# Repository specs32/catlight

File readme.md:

# CATLight (Creativity Art Technology)

The new and shiny Flat Flashlight, now featuring:

- ESP32-S2
- MAX77751
- SK6812 + Cree J-Series
- IMU LSM6DS3
- 3000 mAh LiPo (11.5 Wh)
- more to come

Thank you and have a nice day !

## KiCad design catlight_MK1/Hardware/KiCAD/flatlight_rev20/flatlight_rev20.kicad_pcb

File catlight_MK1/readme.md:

# CATLight (Creativity Art Technology)

This is MARK 1 of the new and shiny ESP32-S2 driven flat flashlight (aka flatlight)

The last flatlight revision was 19 ... I changed naming, and revision number from here on.

So this would be the flatlight REV 20

## This Revision contains multiple errors and has many features missing !!

### The first Pancake never gets right ;)

I release it anyways. Its just my dirty Sandbox to get some mud on my fingers !

thank you and have a nice day !

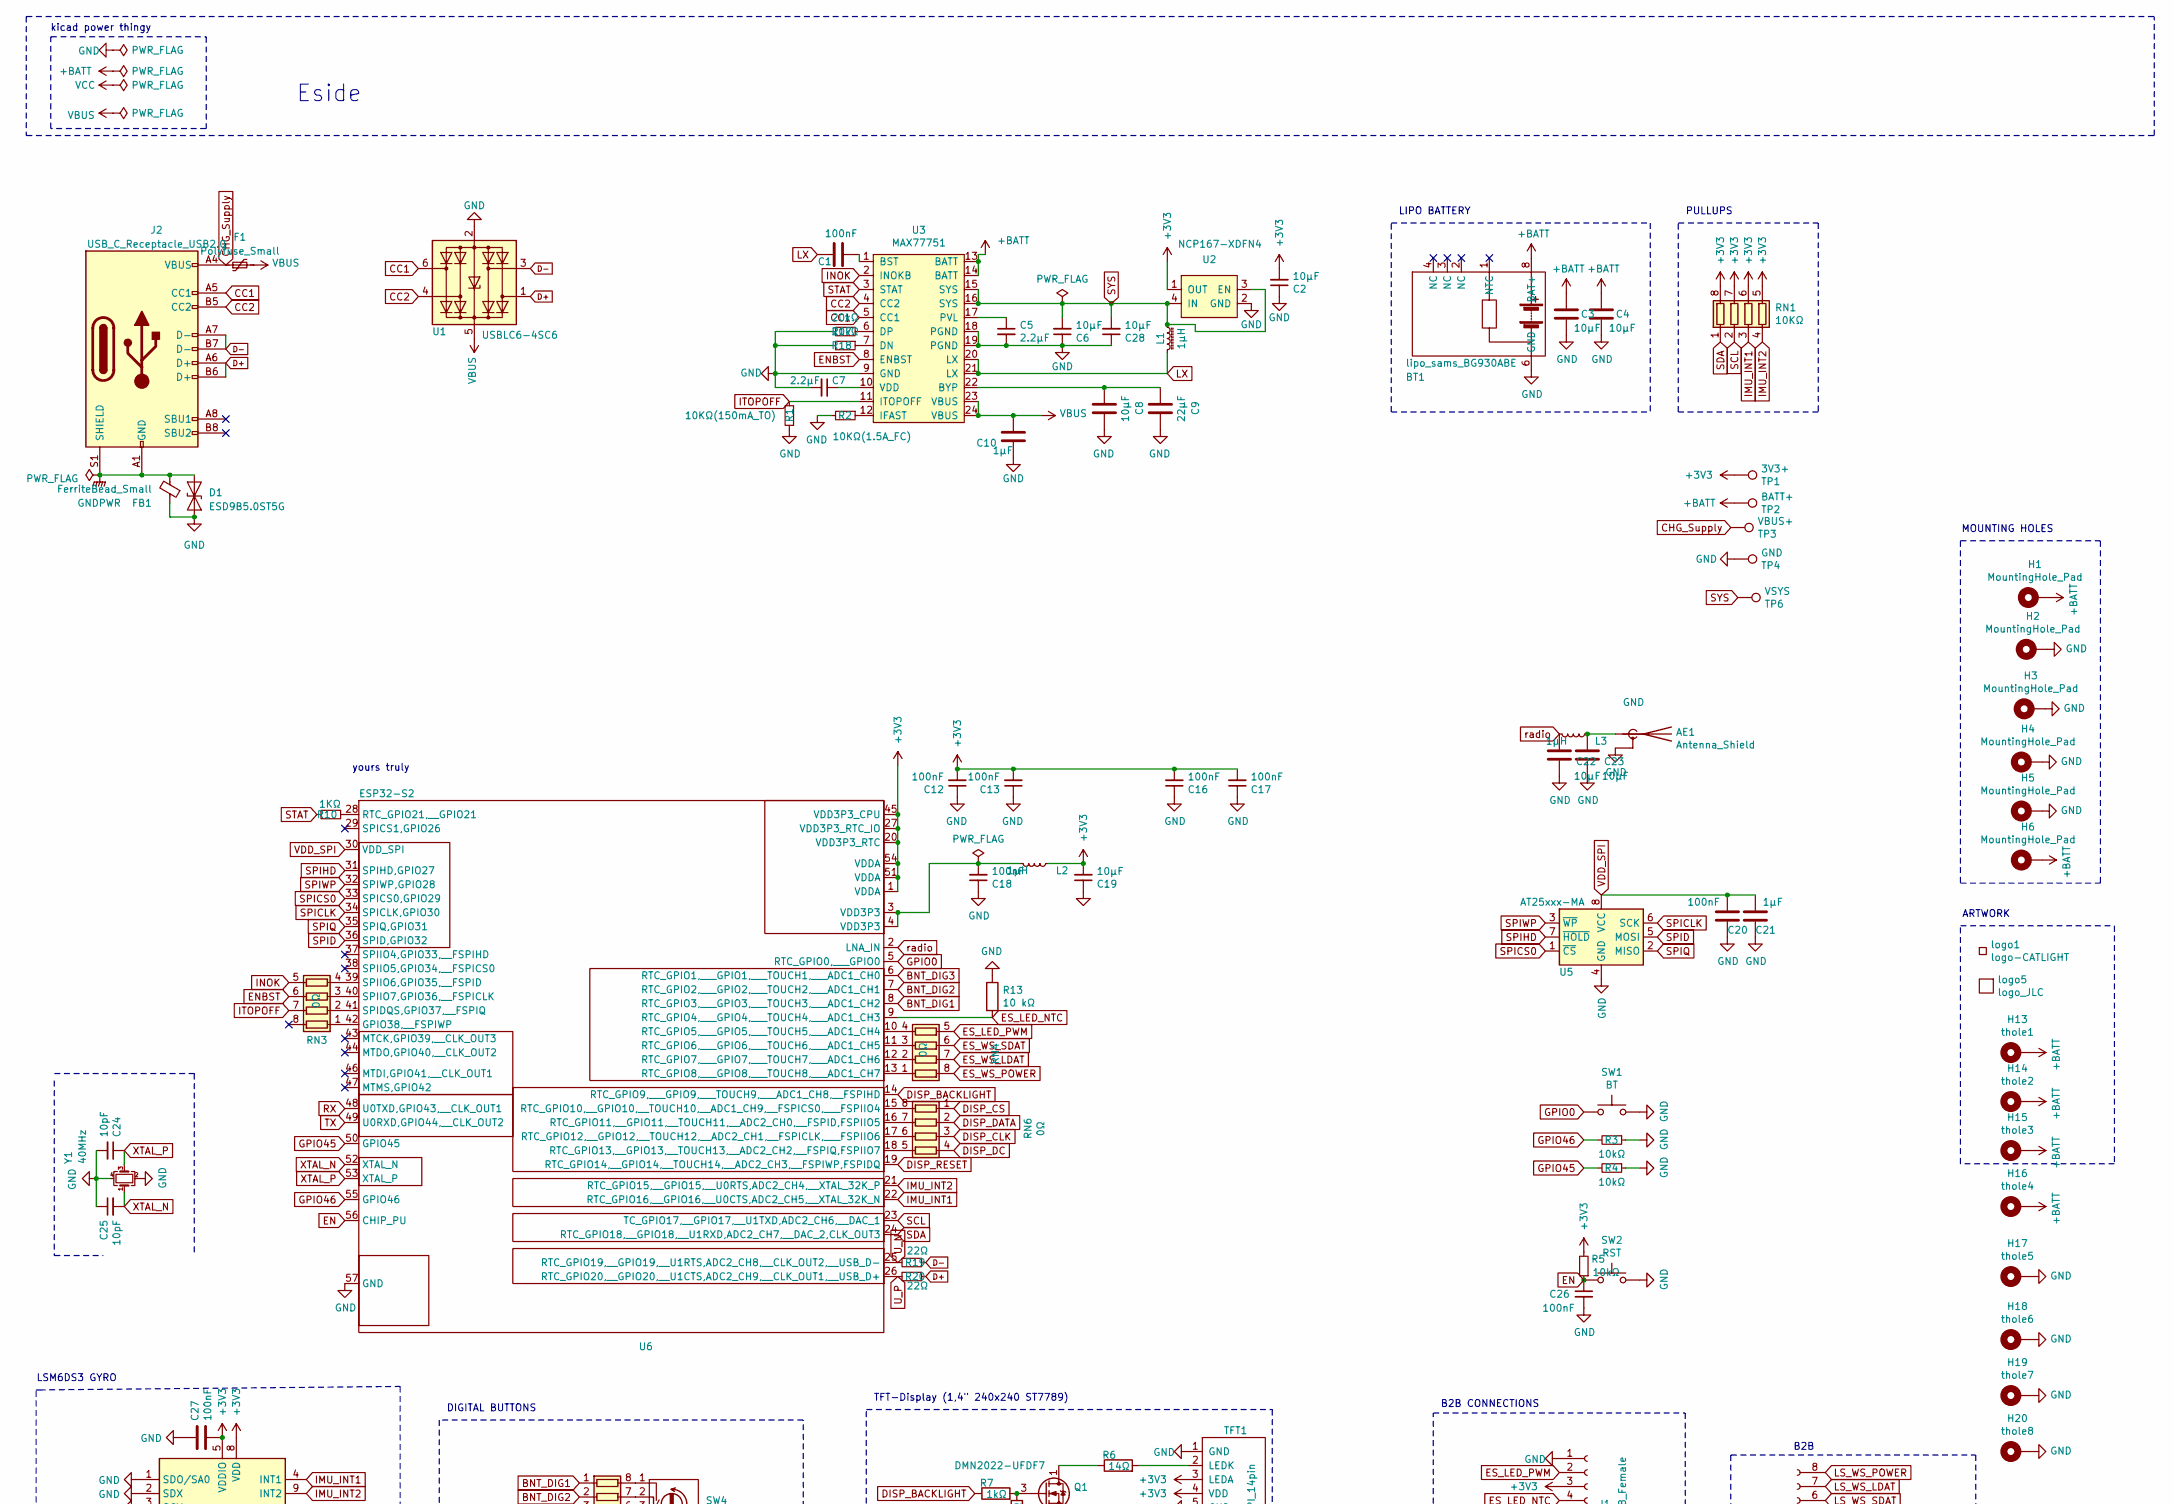
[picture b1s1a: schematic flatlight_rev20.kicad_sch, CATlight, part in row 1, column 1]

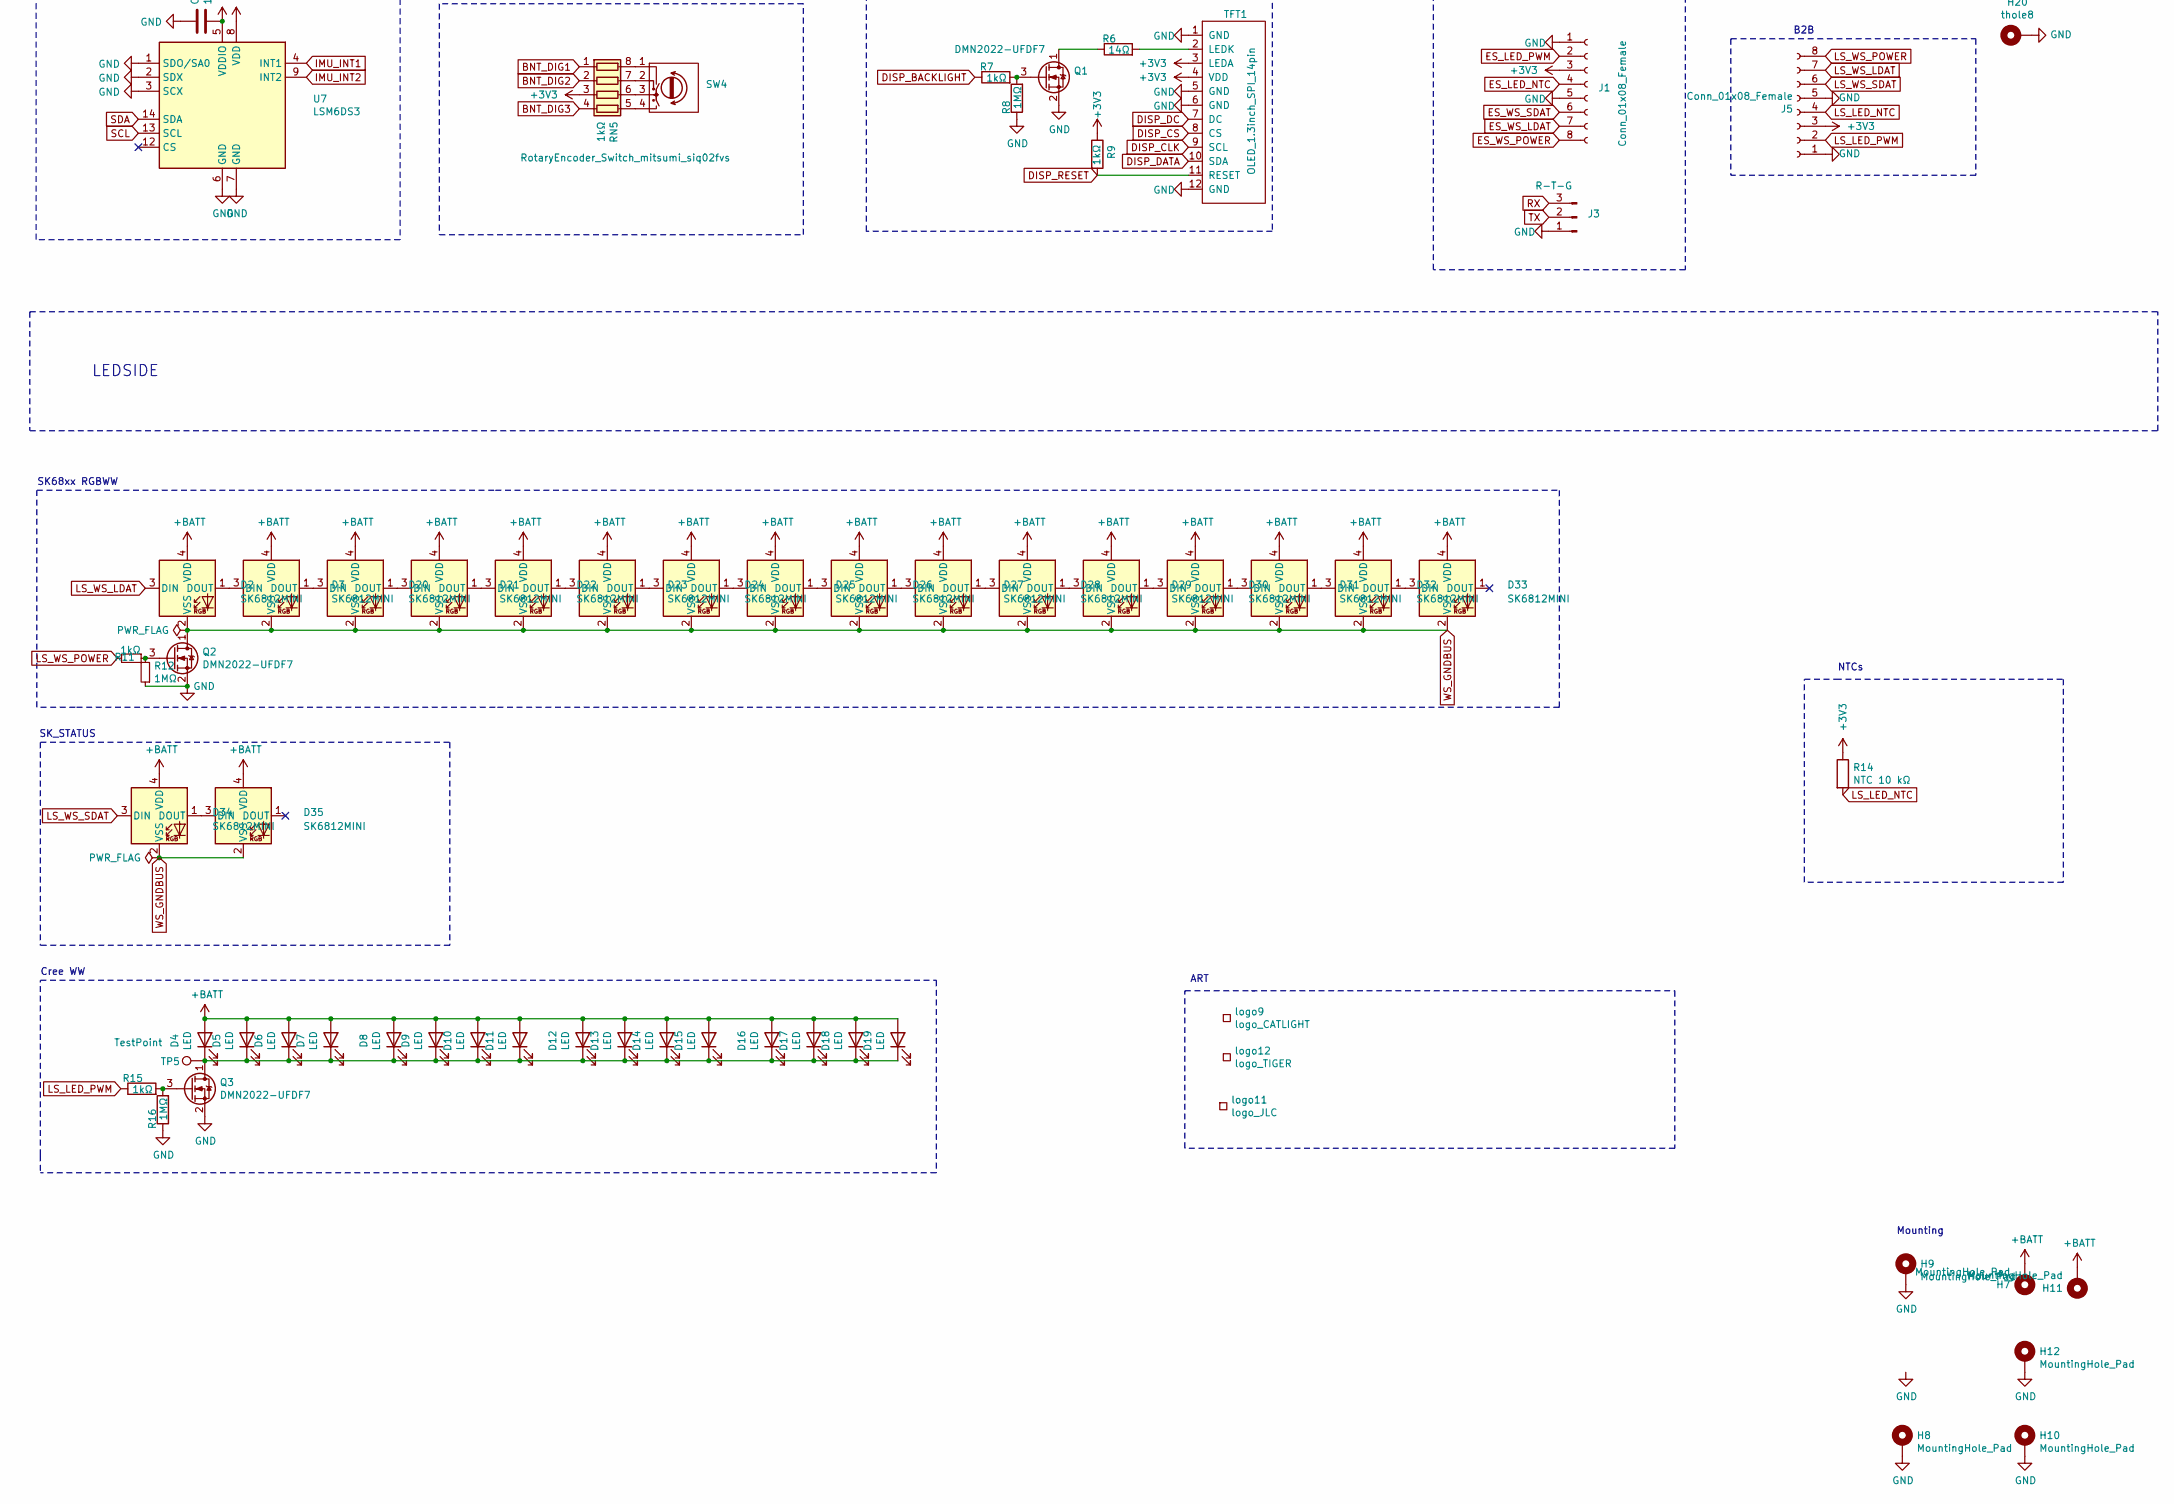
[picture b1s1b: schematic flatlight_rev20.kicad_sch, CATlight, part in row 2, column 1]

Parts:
AE1: Antenna_Shield; Texas_SWRA117D_2.4GHz_Left
BT1: lipo_sams_BG930ABE; lipo_samsung_BG930ABE_double
C1: 100nF; C_0603_1608Metric
C2, C3, C4, C6, C8, C28: 10µF; C_0805_2012Metric
C5, C7: 2.2µF; C_0805_2012Metric
C9: 22µF; C_1210_3225Metric
C10: 1µF; C_0805_2012Metric
C12, C13, C16, C17, C18, C20, C26, C27: 100nF; C_0402_1005Metric
C19, C22, C23: 10µF; C_0603_1608Metric
C21: 1µF; C_0603_1608Metric
C24, C25: 10pF; C_0603_1608Metric
D1: ESD9B5.0ST5G; D_0402_1005Metric_Pad0.77x0.64mm_HandSolder
D2, D20, D21, D22, D23, D24, D25, D26, D27, D28, D29, D30, D31, D32, D33, D34, D35: SK6812MINI; LED_SK6812MINI
D3: SK6812MINI; LED_SK6812MINI_PLCC4_3.5x3.5mm_P1.75mm
D4, D5, D6, D7, D8, D9, D10, D11, D12, D13, D14, D15, D16, D17, D18, D19: LED; LED_Cree-J-Series
F1: Polyfuse_Small; R_0805_2012Metric_Pad1.20x1.40mm_HandSolder
FB1: FerriteBead_Small; R_0805_2012Metric_Pad1.20x1.40mm_HandSolder
H1, H2, H3, H4, H5, H6, H7, H8, H9, H10, H11, H12: MountingHole_Pad; MountingHole_2.2mm_M2_Pad_Via
H13: thole1; plated_hole_1mm
H14: thole2; plated_hole_1mm
H15: thole3; plated_hole_1mm
H16: thole4; plated_hole_1mm
H17: thole5; plated_hole_1mm
H18: thole6; plated_hole_1mm
H19: thole7; plated_hole_1mm
H20: thole8; plated_hole_1mm
J1, J5: Conn_01x08_Female; PinHeader_1x08_P2.00mm_Vertical
J2: USB_C_Receptacle_USB2.0; USB_C_Receptacle_JAE_DX07S016JA1R1500
J3: R-T-G; 01x03_smd_1mmx2mm_pad
L1: 1µH; L_Wuerth_MAPI-4030
L2, L3: 1µH; L_0603_1608Metric
Q1, Q2, Q3: DMN2022-UFDF7; U-DFN2020-6 (Type F)
R1: 10KΩ(150mA_TO); R_0603_1608Metric
R2: 10KΩ(1.5A_FC); R_0603_1608Metric
R3, R4, R5: 10kΩ; R_0603_1608Metric
R6: 14Ω; R_0603_1608Metric
R7, R9, R11, R15: 1kΩ; R_0603_1608Metric
R8, R12, R16: 1MΩ; R_0603_1608Metric
R10: 1KΩ; R_0603_1608Metric
R13: 10 kΩ; R_0603_1608Metric
R14: NTC 10 kΩ; R_0603_1608Metric
R17, R18: 20kΩ; R_0603_1608Metric
R19, R20: 22Ω; R_0603_1608Metric
RN1: 10KΩ; R_Array_Concave_4x0402
RN3, RN4, RN6: 0Ω; R_Array_Concave_4x0402
RN5: 1kΩ; R_Array_Concave_4x0402
SW1: BT; SW_SPST_B3U-1000P
SW2: RST; SW_SPST_B3U-1000P
SW4: RotaryEncoder_Switch_mitsumi_siq02fvs; ROTARY_ENCODER_SIQ_02FVS
TFT1: OLED_1.3inch_SPI_14pin; TFT_1.3inch_spi_12pin_240x240RGB_flat
TP1: 3V3+; TestPoint_Pad_1.0x1.0mm
TP2: BATT+; TestPoint_Pad_1.0x1.0mm
TP3: VBUS+; TestPoint_Pad_1.0x1.0mm
TP4: GND; TestPoint_Pad_1.0x1.0mm
TP5: TestPoint; TestPoint_Pad_1.5x1.5mm
TP6: VSYS; TestPoint_Pad_1.0x1.0mm
U1: USBLC6-4SC6; SOT-23-6
U2: NCP167-XDFN4; UDFN-4-1EP_1x1mm_P0.65mm_EP0.48x0.48mm
U3: MAX77751; max77751
U5: AT25xxx-MA; DFN-8-1EP_3x2mm_P0.5mm_EP1.75x1.45mm
U6: ESP32-S2; QFN-56-1EP_7x7mm_P0.4mm_EP5.6x5.6mm_ThermalVias
U7: LSM6DS3; Bosch_LGA-14_3x2.5mm_P0.5mm
Y1: 40MHz; Crystal_SMD_2520-4Pin_2.5x2.0mm
logo1: logo-CATLIGHT; LOGO_CATLIGHT_4
logo5, logo11: logo_JLC; JLC-SERIAL
logo9: logo_CATLIGHT; LOGO_CATLIGHT_4_small
logo12: logo_TIGER; LOGO_Tiger_1

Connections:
+3V3: C2.2, C12.2, C13.2, C16.2, C17.2, C19.2, C27.2, J1.3, J5.3, L2.1, R5.2, R9.1, R14.1, RN1.5 (R4.2), RN1.6 (R3.2), RN1.7 (R2.2), RN1.8 (R1.2), RN5.3 (R3.1), TFT1.3 (LEDA), TFT1.4 (VDD), TP1.1, U2.1 (OUT), U6.1 (VDDA), U6.20 (VDD3P3_RTC), U6.27 (VDD3P3_RTC_IO), U6.45 (VDD3P3_CPU), U6.51 (VDDA), U6.54 (VDDA), U7.5 (VDDIO), U7.8 (VDD)
+BATT: BT1.7 (BAT+), BT1.8 (BAT+), C3.1, C4.1, D2.4 (VDD), D3.4 (VDD), D4.2 (A), D5.2 (A), D6.2 (A), D7.2 (A), D8.2 (A), D9.2 (A), D10.2 (A), D11.2 (A), D12.2 (A), D13.2 (A), D14.2 (A), D15.2 (A), D16.2 (A), D17.2 (A), D18.2 (A), D19.2 (A), D20.4 (VDD), D21.4 (VDD), D22.4 (VDD), D23.4 (VDD), D24.4 (VDD), D25.4 (VDD), D26.4 (VDD), D27.4 (VDD), D28.4 (VDD), D29.4 (VDD), D30.4 (VDD), D31.4 (VDD), D32.4 (VDD), D33.4 (VDD), D34.4 (VDD), D35.4 (VDD), H1.1, H6.1, H7.1, H11.1, H13.1, H14.1, H15.1, H16.1, TP2.1, U3.13 (BATT), U3.14 (BATT)
BNT_DIG1: RN5.1 (R1.1), U6.8 (RTC_GPIO3,___GPIO3,___TOUCH3,___ADC1_CH2)
BNT_DIG2: RN5.2 (R2.1), U6.7 (RTC_GPIO2,___GPIO2,___TOUCH2,___ADC1_CH1)
BNT_DIG3: RN5.4 (R4.1), U6.6 (RTC_GPIO1,___GPIO1,___TOUCH1,___ADC1_CH0)
CC1: J2.A5 (CC1), U1.6 (I/O4), U3.5 (CC1)
CC2: J2.B5 (CC2), U1.4 (I/O3), U3.4 (CC2)
CHG_Supply: F1.1, J2.A4 (VBUS), J2.A9 (VBUS), J2.B4 (VBUS), J2.B9 (VBUS), TP3.1
D+: J2.A6 (D+), J2.B6 (D+), R20.1, U1.1 (I/O1)
D-: J2.A7 (D-), J2.B7 (D-), R19.1, U1.3 (I/O2)
DISP_BACKLIGHT: R7.1, U6.14 (RTC_GPIO9,___GPIO9,___TOUCH9,___ADC1_CH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)
DISP_CLK: RN6.3 (R3.1), TFT1.9 (SCL)
DISP_CS: RN6.1 (R1.1), TFT1.8 (CS)
DISP_DATA: RN6.2 (R2.1), TFT1.10 (SDA)
DISP_DC: RN6.4 (R4.1), TFT1.7 (DC)
DISP_RESET: R9.2, TFT1.11 (RESET), U6.19 (RTC_GPIO14,__GPIO14,__TOUCH14,__ADC2_CH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)
EN: C26.1, R5.1, SW2.1, U6.56 (CHIP_PU)
ENBST: RN3.6 (R3.2), U3.8 (ENBST)
ES_LED_NTC: J1.4, R13.2, U6.9 (RTC_GPIO4,___GPIO4,___TOUCH4,___ADC1_CH3)
ES_LED_PWM: J1.2, RN4.5 (R4.2)
ES_WS_LDAT: J1.7, RN4.7 (R2.2)
ES_WS_POWER: J1.8, RN4.8 (R1.2)
ES_WS_SDAT: J1.6, RN4.6 (R3.2)
GND: AE1.2 (Shield), BT1.5 (GND), BT1.6 (GND), C2.1, C3.2, C4.2, C5.2, C6.1, C7.2, C8.2, C9.2, C10.1, C12.1, C13.1, C16.1, C17.1, C18.1, C19.1, C20.1, C21.1, C22.1, C23.1, C24.2, C25.1, C26.2, C27.1, C28.1, D1.1 (A1), FB1.1, H2.1, H3.1, H4.1, H5.1, H8.1, H9.1, H10.1, H12.1, H17.1, H18.1, H19.1, H20.1, J1.1, J1.5, J3.1, J5.1, J5.5, Q1.2 (S), Q2.2 (S), Q3.2 (S), R1.1, R2.2, R3.1, R4.1, R8.1, R12.1, R13.1, R16.1, R17.2, R18.2, SW1.2, SW2.2, TFT1.1 (GND), TFT1.5 (GND), TFT1.6 (GND), TFT1.12 (GND), TP4.1, U1.2 (GND), U2.2 (GND), U2.5 (GND), U3.9 (GND), U3.18 (PGND), U3.19 (PGND), U5.4 (GND), U5.9 (GND), U6.57 (GND), U7.1 (SDO/SA0), U7.2 (SDX), U7.3 (SCX), U7.6 (GND), U7.7 (GND), Y1.2, Y1.4
GNDPWR: D1.2 (A2), FB1.2, J2.A1 (GND), J2.A12 (GND), J2.B1 (GND), J2.B12 (GND), J2.S1 (SHIELD)
GPIO0: SW1.1, U6.5 (RTC_GPIO0,___GPIO0)
GPIO45: R4.2, U6.50 (GPIO45)
GPIO46: R3.2, U6.55 (GPIO46)
IMU_INT1: RN1.3 (R3.1), U6.22 (RTC_GPIO16,__GPIO16,__U0CTS,ADC2_CH5,__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), U7.4 (INT1)
IMU_INT2: RN1.4 (R4.1), U6.21 (RTC_GPIO15,__GPIO15,__U0RTS,ADC2_CH4,__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), U7.9 (INT2)
INOK: RN3.5 (R4.2), U3.2 (INOKB)
ITOPOFF: R1.2, RN3.7 (R2.2), U3.11 (ITOPOFF)
LS_LED_NTC: J5.4, R14.2
LS_LED_PWM: J5.2, R15.1
LS_WS_LDAT: D2.3 (DIN), J5.7
LS_WS_POWER: J5.8, R11.2
LS_WS_SDAT: D34.3 (DIN), J5.6
LX: C1.2, L1.2, U3.20 (LX), U3.21 (LX)
unnamed: AE1.1 (A), C23.2, L3.1
unnamed: C1.1, U3.1 (BST)
unnamed: C5.1, U3.17 (PVL)
unnamed: C7.1, U3.10 (VDD)
unnamed: C8.1, C9.1, U3.22 (BYP)
unnamed: C18.2, L2.2, U6.3 (VDD3P3), U6.4 (VDD3P3)
unnamed: D2.1 (DOUT), D3.3 (DIN)
unnamed: D4.1 (K), D5.1 (K), D6.1 (K), D7.1 (K), D8.1 (K), D9.1 (K), D10.1 (K), D11.1 (K), D12.1 (K), D13.1 (K), D14.1 (K), D15.1 (K), D16.1 (K), D17.1 (K), D18.1 (K), D19.1 (K), Q3.1 (D), TP5.1
unnamed: D20.1 (DOUT), D21.3 (DIN)
unnamed: D3.1 (DOUT), D20.3 (DIN)
unnamed: D21.1 (DOUT), D22.3 (DIN)
unnamed: D22.1 (DOUT), D23.3 (DIN)
unnamed: D23.1 (DOUT), D24.3 (DIN)
unnamed: D24.1 (DOUT), D25.3 (DIN)
unnamed: D25.1 (DOUT), D26.3 (DIN)
unnamed: D26.1 (DOUT), D27.3 (DIN)
unnamed: D27.1 (DOUT), D28.3 (DIN)
unnamed: D28.1 (DOUT), D29.3 (DIN)
unnamed: D29.1 (DOUT), D30.3 (DIN)
unnamed: D30.1 (DOUT), D31.3 (DIN)
unnamed: D31.1 (DOUT), D32.3 (DIN)
unnamed: D32.1 (DOUT), D33.3 (DIN)
unnamed: D34.1 (DOUT), D35.3 (DIN)
unnamed: Q1.1 (D), R6.1
unnamed: Q1.3 (G), R7.2, R8.2
unnamed: Q2.3 (G), R11.1, R12.2
unnamed: Q3.3 (G), R15.2, R16.2
unnamed: R2.1, U3.12 (IFAST)
unnamed: R6.2, TFT1.2 (LEDK)
unnamed: R10.1, U6.28 (RTC_GPIO21,__GPIO21)
unnamed: R17.1, U3.6 (DP)
unnamed: R18.1, U3.7 (DN)
unnamed: RN3.1 (R1.1), U6.42 (GPIO38,__FSPIWP)
unnamed: RN3.2 (R2.1), U6.41 (SPIDQS,GPIO37,__FSPIQ)
unnamed: RN3.3 (R3.1), U6.40 (SPIIO7,GPIO36,__FSPICLK)
unnamed: RN3.4 (R4.1), U6.39 (SPIIO6,GPIO35,__FSPID)
unnamed: RN4.1 (R1.1), U6.13 (RTC_GPIO8,___GPIO8,___TOUCH8,___ADC1_CH7)
unnamed: RN4.2 (R2.1), U6.12 (RTC_GPIO7,___GPIO7,___TOUCH7,___ADC1_CH6)
unnamed: RN4.3 (R3.1), U6.11 (RTC_GPIO6,___GPIO6,___TOUCH6,___ADC1_CH5)
unnamed: RN4.4 (R4.1), U6.10 (RTC_GPIO5,___GPIO5,___TOUCH5,___ADC1_CH4)
unnamed: RN5.5 (R4.2), SW4.4 (B)
unnamed: RN5.6 (R3.2), SW4.3 (C)
unnamed: RN5.7 (R2.2), SW4.2 (S)
unnamed: RN5.8 (R1.2), SW4.1 (A)
unnamed: RN6.5 (R4.2), U6.18 (RTC_GPIO13,__GPIO13,__TOUCH13,__ADC2_CH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)
unnamed: RN6.6 (R3.2), U6.17 (RTC_GPIO12,__GPIO12,__TOUCH12,__ADC2_CH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)
unnamed: RN6.7 (R2.2), U6.16 (RTC_GPIO11,__GPIO11,__TOUCH11,__ADC2_CH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)
unnamed: RN6.8 (R1.2), U6.15 (RTC_GPIO10,__GPIO10,__TOUCH10,__ADC1_CH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)
RX: J3.3, U6.48 (U0TXD,GPIO43,__CLK_OUT1)
SCL: RN1.2 (R2.1), U6.23 (TC_GPIO17,__GPIO17,__U1TXD,ADC2_CH6,__D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), U7.13 (SCL)
SDA: RN1.1 (R1.1), U6.24 (RTC_GPIO18,__GPIO18,__U1RXD,ADC2_CH7,__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), U7.14 (SDA)
SPICLK: U5.6 (SCK), U6.34 (SPICLK,GPIO30)
SPICS0: U5.1 (~CS), U6.33 (SPICS0,GPIO29)
SPID: U5.5 (MOSI), U6.36 (SPID,GPIO32)
SPIHD: U5.7 (~HOLD), U6.31 (SPIHD,GPIO27)
SPIQ: U5.2 (MISO), U6.35 (SPIQ,GPIO31)
SPIWP: U5.3 (~WP), U6.32 (SPIWP,GPIO28)
STAT: R10.2, U3.3 (STAT)
SYS: C6.2, C28.2, L1.1, TP6.1, U2.3 (EN), U2.4 (IN), U3.15 (SYS), U3.16 (SYS)
TX: J3.2, U6.49 (U0RXD,GPIO44,__CLK_OUT2)
U_N: R19.2, U6.25 (RTC_GPIO19,__GPIO19,__U1RTS,ADC2_CH8,__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)
U_P: R20.2, U6.26 (RTC_GPIO20,__GPIO20,__U1CTS,ADC2_CH9,__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)
VBUS: C10.2, F1.2, U1.5 (VBUS), U3.23 (VBUS), U3.24 (VBUS)
VDD_SPI: C20.2, C21.2, U5.8 (VCC), U6.30 (VDD_SPI)
WS_GNDBUS: D2.2 (VSS), D3.2 (VSS), D20.2 (VSS), D21.2 (VSS), D22.2 (VSS), D23.2 (VSS), D24.2 (VSS), D25.2 (VSS), D26.2 (VSS), D27.2 (VSS), D28.2 (VSS), D29.2 (VSS), D30.2 (VSS), D31.2 (VSS), D32.2 (VSS), D33.2 (VSS), D34.2 (VSS), D35.2 (VSS), Q2.1 (D)
XTAL_N: C25.2, U6.52 (XTAL_N), Y1.1
XTAL_P: C24.1, U6.53 (XTAL_P), Y1.3
radio: C22.2, L3.2, U6.2 (LNA_IN)

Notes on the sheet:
LSM6DS3 GYRO
SK68xx RGBWW
kicad power thingy
Cree WW
SK_STATUS
LEDSIDE
yours truly
Eside
DIGITAL BUTTONS
TFT-Display (1,4" 240x240 ST7789)
ART
LIPO BATTERY
B2B CONNECTIONS
PULLUPS
B2B
NTCs
Mounting
MOUNTING HOLES
ARTWORK

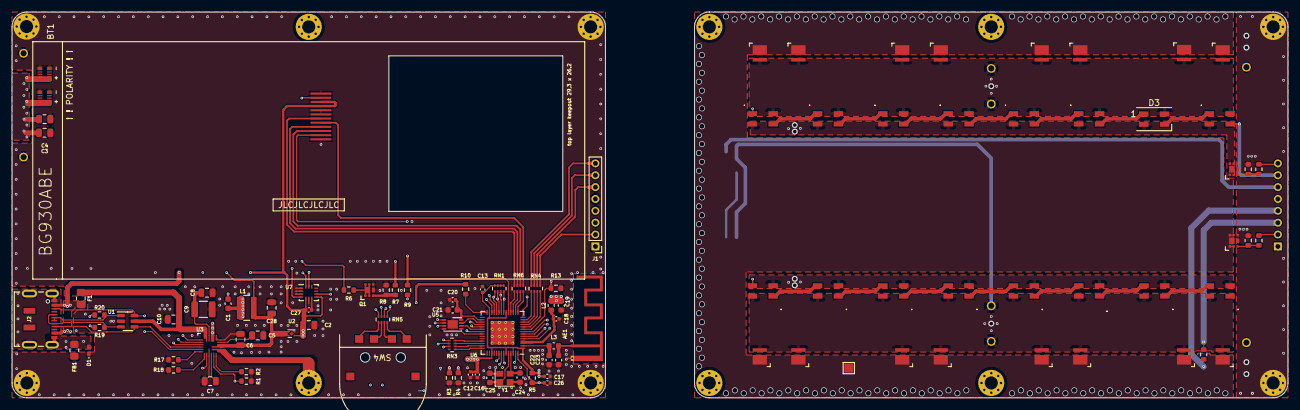
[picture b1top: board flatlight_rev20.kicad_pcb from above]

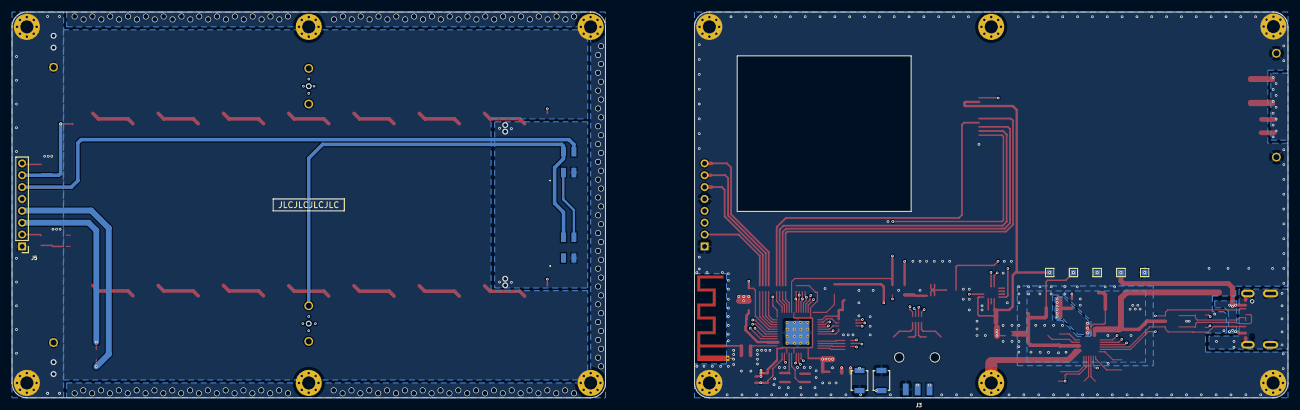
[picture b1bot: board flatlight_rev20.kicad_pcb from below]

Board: 4 copper layers, 215.0 x 65.0 mm, 141 parts (15 on the bottom side), 106 nets.

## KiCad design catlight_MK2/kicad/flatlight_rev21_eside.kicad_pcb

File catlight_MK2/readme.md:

# CATLight (Creativity Art Technology)

This is MARK 2 of the new and shiny ESP32-S2 driven flat flashlight (aka flatlight)

This is a close proximity Flashlight, it has no lense to focus a beam, but it smoothly lights up a wide field around you. I find it perfect for indoor usage (searching dark drawers in the cellar and so on, but it also lights your way to the shed at night..)

Features : 
- USB-C power delivery standard realized with a MAX77751 (fast charge + PD (boost mode 5V up to 1 Amp))
- ESP32-S2 with wifi etc...
- 1.2 " TFT SPI color display
- 1 IMU LSM6DS3 or LSM6DSM .. both will work with slight changes in the initialization
- 1 CREE XLAMP with a DIO5661 flash driver and protective lens (no focus) that delivers up to 1.5 Amps into the XLAMP.. makes for a nice foto flash ..
- 16 neopixels on there 2 rows by 8.. i think it is possible to realize a POV display with it since there also is a LSM6DS3 IMU on there.
- 10 Duris high power LEDs (100mA each) this is the main light source (300 mA J-Series are no longer available.. sadly !)
- 4 TEMP sensors on the light. 2 NTCs close to critical places (XLAMP and Duris LEDS) 1 in the ESP itself and on in the IMU.
- Battery Voltage measuring (resistor divider on analog 1)

### This Revision works ! 

... with no errors as far as I can see and test (I own no OSZI ;))

There is one thing though... the Antenna matching Network works better if you put a cap in series and the coil in the first place to ground. (swap C24 with L3)

This revision works with WLED beta 2 (0.13.0-b2) there are filesystem issues, but the default install seems to work and you can save the LED settings and power off / on again and it maintains theses settings even there is no "official" support for the ESP32-S2 yet.
MAYBE I will fork and branch and modify and write a usermod for wled in the future. Maybe...
For now there is rudimentary arduino firmware in the arduino folder.
There is a platformio_override.ini in the base Folder I used to compile WLED with in code OSS with platformio under arch linux.

#### WARNING !!! WARNING !!! WARNING !!! WARNING !!! WARNING !!! WARNING !!! WARNING !!! WARNING !!! 

DO NOT put too much capacitance on the LED side, it will mess with the soft latch ! 1µF per duris LED is sufficient and works.
If you put a lot of high value CAPs on the LED side you need to lower the value of R5. (1.2KΩ with 25 µF on the LED side. Flash and array)

the duris LEDs are mosfet driven and that is their ONE and ONLY current limiter, a duty cycle of 30 % on a full lipo makes a nice bright light.
if you pull up the mosfet with 100 % duty cycle it make a smoldered PCB with the LEDs falling off and molten solder dripping everywhere... 
probably a good idea to keep that in mind when fumbling with the firmware...
___

there is a footprint for additional flash memory with a solder bridge CS0/CS1 parallel to the internal flash. if you have an ESP32-S2 without flash you can put a flash chip here (AT256Q i think) please refer to the flash compatibility list for the ESP32-S2 on the espressif website.

wifi standby time with a genuine LIPO Battery is 60+ hours

USB-C fast charging works up to 2.5 Ampere !! (almost full in 60 minutes ;))
the MAX 77751 supports pass through and power delivery, so you can charge your phne on the light in an emerrgency !

Please keep in mind that this project is my private experiment and CC-BY-NC-SA !
If you blow up your toaster .. not my fault.

the overall development cost was 600 €, the cost per CATLight (PCB + parts + 3dprint) is around 50 € assembly time is 6-8 hours if you do it 100% by hand.

Have fun emitting Bosons of differend wavelength..

made with <3 btw!

#### Special thanks to Lisa who provided all the cat drawings !!!
___
___

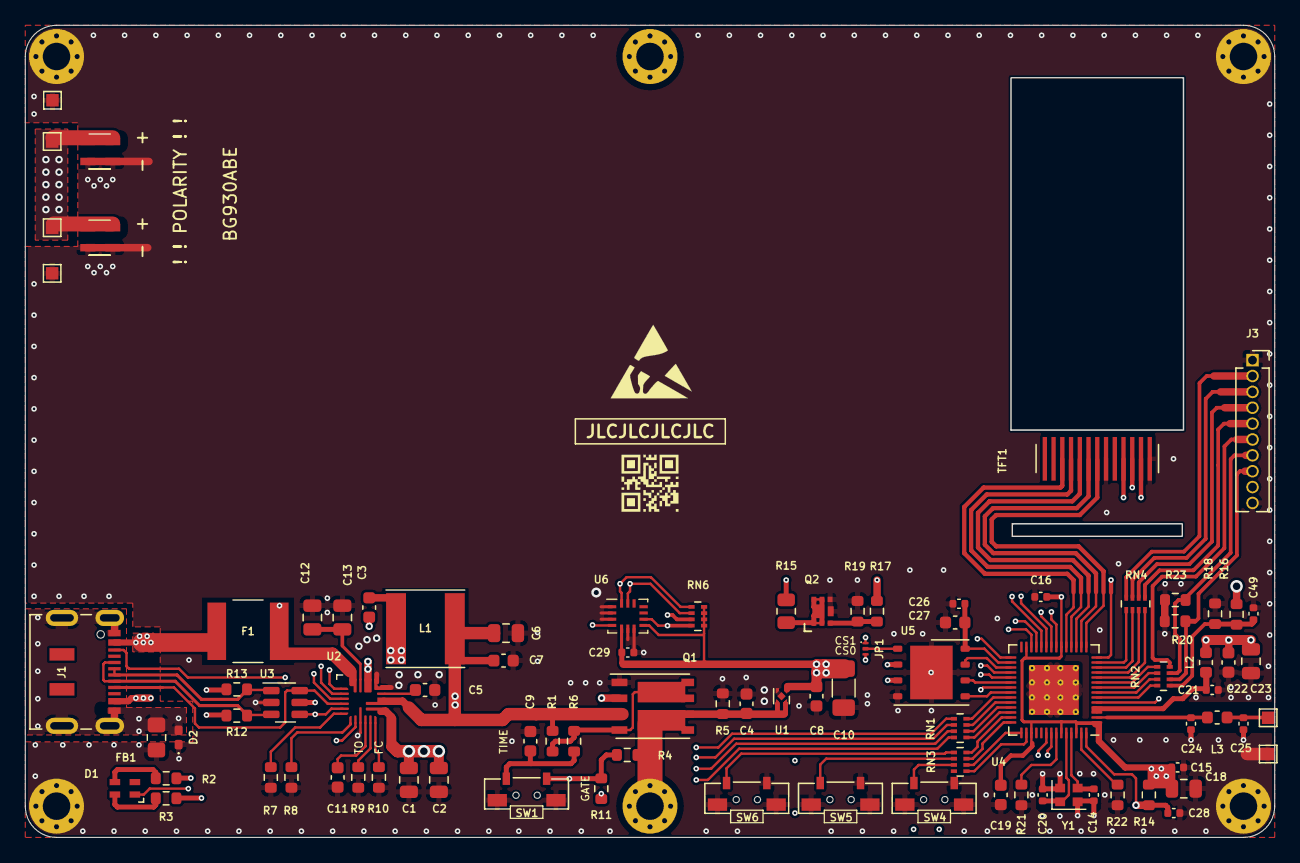
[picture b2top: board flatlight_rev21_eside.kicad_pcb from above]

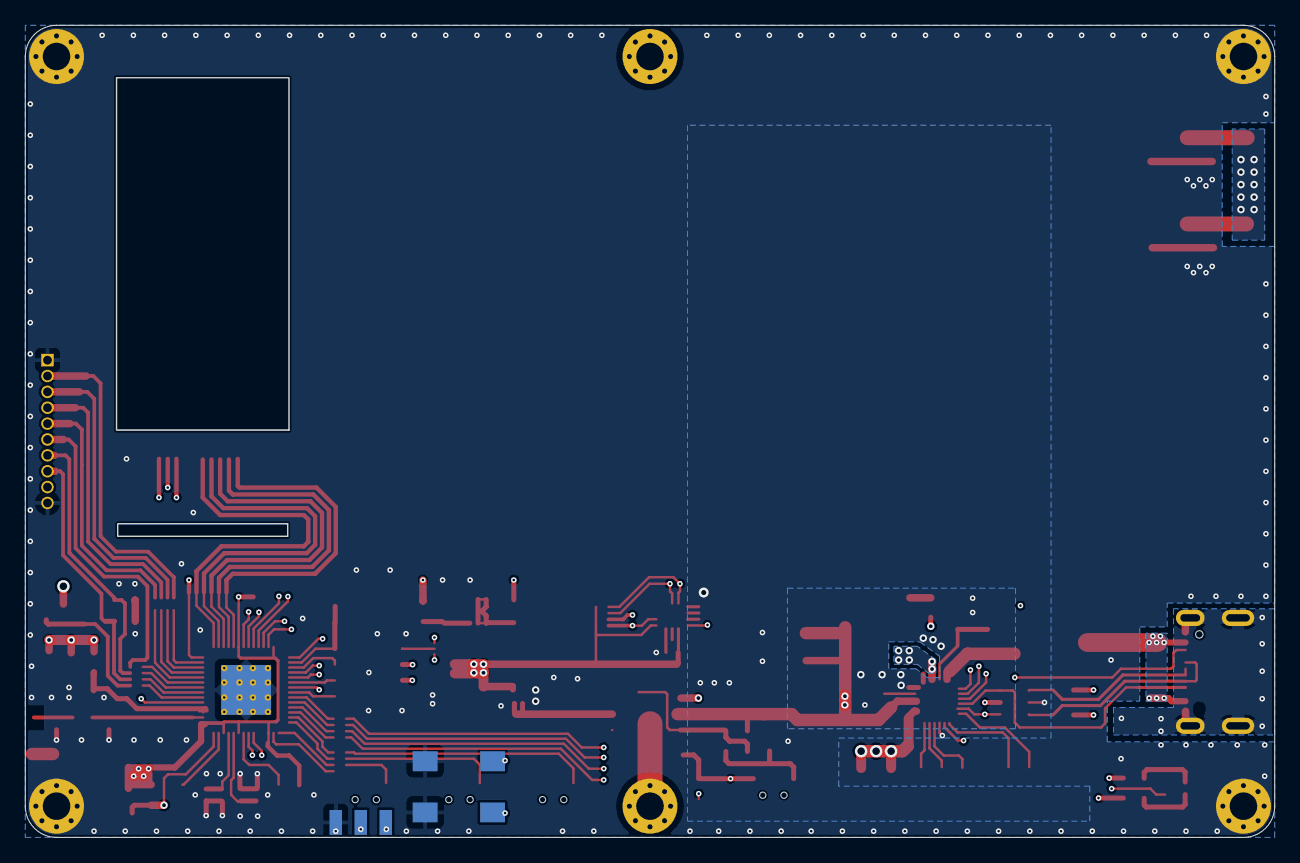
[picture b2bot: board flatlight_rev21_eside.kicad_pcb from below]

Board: 4 copper layers, 100.0 x 65.0 mm, 102 parts (5 on the bottom side), 92 nets.

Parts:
BT1: lipo_sams_BG930ABE; lipo_samsung_BG930ABE_double
C1, C2, C6, C12, C18, C23: 10µF; C_0805_2012Metric
C3: 100nF; C_0603_1608Metric
C4, C7, C8, C9, C19, C22, C27: 1µF; C_0603_1608Metric
C5, C11: 2.2µF; C_0603_1608Metric
C10: 10µF; C_1206_3216Metric_Pad1.33x1.80mm_HandSolder
C13: 22µF; C_0805_2012Metric
C14, C20: 10pF; C_0402_1005Metric
C15, C16, C21, C26, C28, C29, C49: 100nF; C_0402_1005Metric
C24, C25: 4,7 pF; C_0402_1005Metric
D1: LED_ABRG; 0606_ARGB_LED
D2: ESD9B5.0ST5G; D_0402_1005Metric_Pad0.77x0.64mm_HandSolder
F1: Polyfuse_Small; FUSE_littlefuse_2016-4.1x5.2mm
FB1: FerriteBead_Small; R_0805_2012Metric_Pad1.20x1.40mm_HandSolder
H1, H2, H3, H4, H5, H6: MountingHole_Pad; MountingHole_2.2mm_M2_Pad_Via
J1: USB_C_Receptacle_USB2.0; USB_C_Receptacle_JAE_DX07S016JA1R1500
J2: G-T-R; 01x03_smd_1mmx2mm_pad
J3: B2B_eside; PinSocket_1x10_P1.27mm_Vertical
JP1: SolderJumper_3_Open; microbridge
L1: 1µH; L_Taiyo-Yuden_NR-60xx
L2: 1µH; L_0603_1608Metric
L3: 1.8 nH; L_0603_1608Metric
Q1: DMC1016UPD; PowerDI5060-8
Q2: DMN2022-UFDF7; U-DFN2020-6 (Type F)
R1, R4, R14, R21, R22: 10kΩ; R_0603_1608Metric
R2, R3: 1KΩ; R_0603_1608Metric
R5: 10kΩ (depending on caps); R_0603_1608Metric
R6: 100kΩ; R_0603_1608Metric
R7, R8: 20kΩ; R_0603_1608Metric
R9: 10KΩ(150mA_TO); R_0603_1608Metric
R10: 10KΩ(1.5A_FC); R_0603_1608Metric
R11: 0 Ω; R_0603_1608Metric
R12, R13: 22Ω; R_0603_1608Metric
R15: 14Ω; R_0805_2012Metric
R16, R18, R19: 1MΩ; R_0603_1608Metric
R17: 1kΩ; R_0603_1608Metric
R20, R23: 10 kΩ; R_0603_1608Metric
RN1, RN2, RN3: 0Ω; R_Array_Concave_4x0402
RN4: 1kΩ; R_Array_Concave_4x0402
RN6: 10KΩ; R_Array_Concave_4x0402
SW1, SW4, SW5, SW6: BTN_PWR; white_nano_smd_switch
SW2: BT; SW_SPST_EVQPE1
SW3: RST; SW_SPST_EVQPE1
TFT1: OLED_ST7735_0.9inch_SPI_13pin; TFT_ST7735_0,96_160x80_folded
TP6: ANT_H; TestPoint_Pad_1.0x1.0mm
TP8: ANT_GND; TestPoint_Pad_1.0x1.0mm
TP11, TP12: GND; TestPoint_Pad_1.0x1.0mm
TP13, TP14: +BATT; TestPoint_Pad_1.0x1.0mm
U1: NCP167-XDFN4; UDFN-4-1EP_1x1mm_P0.65mm_EP0.48x0.48mm
U2: MAX77751; max77751
U3: USBLC6-4SC6; SOT-23-6
U4: ESP32-S2; QFN-56-1EP_7x7mm_P0.4mm_EP5.6x5.6mm_ThermalVias
U5: AT25xxx-MA; WSON-8-1EP_6x5mm_P1.27mm_EP3.4x4.3mm
U6: LSM6DS3; Bosch_LGA-14_3x2.5mm_P0.5mm
Y1: 40MHz; Crystal_SMD_2016-4Pin_2.0x1.6mm_smallpads
logo1: logo_qrtag; logo_QR_url_git_catlight
logo2: logo_JLC; JLC-SERIAL
logo6: logo_esd; ESD-Logo_6.6x6mm_SilkScreen
logo8: logo_heart; logo_heart3
logo10: logo_CATLIGHT; logo_catlightMK2_small

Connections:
+3V3: C8.2, C10.2, C15.2, C16.2, C18.2, C19.2, C22.2, C23.2, C29.2, J3.9, L2.1, R14.2, RN6.5 (R4.2), RN6.6 (R3.2), RN6.7 (R2.2), RN6.8 (R1.2), TFT1.10 (VCC), TFT1.12 (LEDA), U1.1 (OUT), U4.1 (VDDA), U4.20 (VDD3P3_RTC), U4.27 (VDD3P3_RTC_IO), U4.45 (VDD3P3_CPU), U4.51 (VDDA), U4.54 (VDDA), U6.5 (VDDIO), U6.8 (VDD)
+BATT: BT1.7 (+), BT1.8 (+), C1.2, C2.2, R16.2, TP13.1, TP14.1, U2.13 (BATT), U2.14 (BATT)
ADC_BATV: C49.1, R16.1, R18.2, RN2.5 (R4.2)
BNT_DIG1: RN3.5 (R4.2), SW6.2
BNT_DIG2: RN3.6 (R3.2), SW5.2
BNT_DIG3: RN3.7 (R2.2), SW4.2
CC1: J1.A5 (CC1), U2.5 (CC1), U3.4 (I/O3)
CC2: J1.B5 (CC2), U2.4 (CC2), U3.6 (I/O4)
D+: J1.A6 (D+), J1.B6 (D+), R13.1, U3.1 (I/O1)
D-: J1.A7 (D-), J1.B7 (D-), R12.1, U3.3 (I/O2)
DISP_BACKLIGHT: R17.1, U4.14 (RTC_GPIO9,___GPIO9,___TOUCH9,___ADC1_CH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)
DISP_CLK: TFT1.4 (SCK), U4.18 (RTC_GPIO13,__GPIO13,__TOUCH13,__ADC2_CH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)
DISP_CS: TFT1.7 (CS), U4.15 (RTC_GPIO10,__GPIO10,__TOUCH10,__ADC1_CH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)
DISP_DATA: TFT1.3 (MOSI), U4.19 (RTC_GPIO14,__GPIO14,__TOUCH14,__ADC2_CH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)
DISP_DC: TFT1.5 (RS), U4.17 (RTC_GPIO12,__GPIO12,__TOUCH12,__ADC2_CH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)
DISP_RESET: TFT1.6 (RES), U4.16 (RTC_GPIO11,__GPIO11,__TOUCH11,__ADC2_CH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)
EN: C28.1, R14.1, SW3.1, U4.56 (CHIP_PU)
ENBST: RN1.5 (R4.2), U2.8 (ENBST)
ES_FLASH_EN: J3.3, RN4.7 (R2.2)
ES_JS_LED_NTC: J3.8, R20.2, RN2.6 (R3.2)
ES_LED_PWM: J3.2, RN4.8 (R1.2)
ES_TORCH_EN: J3.4, RN4.6 (R3.2)
ES_WS_LDAT: J3.5, RN4.5 (R4.2)
ES_WS_POWER: J3.6, RN2.8 (R1.2)
ES_XP_LED_NTC: J3.7, R23.2, RN2.7 (R2.2)
GND: BT1.5 (-), BT1.6 (-), C1.1, C2.1, C4.1, C5.2, C6.1, C7.1, C8.1, C9.2, C10.1, C11.2, C12.2, C13.2, C14.2, C15.1, C16.1, C18.1, C19.1, C20.1, C21.1, C22.1, C23.1, C24.1, C25.1, C26.1, C27.1, C28.2, C29.1, C49.2, D2.1 (A1), FB1.1, H2.1, H3.1, H4.1, H5.1, J2.1, J3.1, J3.10, Q1.1 (S), Q2.2 (S), R5.2, R7.2, R8.2, R9.1, R10.2, R18.1, R19.1, R20.1, R21.1, R22.1, R23.1, SW1.3, SW2.2, SW3.2, SW4.1, SW4.3, SW5.1, SW5.3, SW6.1, SW6.3, TFT1.8 (GND), TFT1.13 (GND), TP8.1, TP11.1, TP12.1, U1.2 (GND), U1.5 (GND), U2.9 (GND), U2.18 (PGND), U2.19 (PGND), U3.2 (GND), U4.57 (GND), U5.4 (GND), U5.9 (GND), U6.1 (SDO/SA0), U6.2 (SDX), U6.3 (SCX), U6.6 (GND), U6.7 (GND), Y1.2, Y1.4
GNDPWR: D2.2 (A2), FB1.2, J1.A1 (GND), J1.A12 (GND), J1.B1 (GND), J1.B12 (GND), J1.S1 (SHIELD)
GPIO0: SW2.1, U4.5 (RTC_GPIO0,___GPIO0)
GPIO45: R21.2, U4.50 (GPIO45)
GPIO46: R22.2, U4.55 (GPIO46)
IMU_INT1: RN6.3 (R3.1), U4.22 (RTC_GPIO16,__GPIO16,__U0CTS,ADC2_CH5,__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), U6.4 (INT1)
IMU_INT2: RN6.4 (R4.1), U4.21 (RTC_GPIO15,__GPIO15,__U0RTS,ADC2_CH4,__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), U6.9 (INT2)
INOK: R2.2, RN1.7 (R2.2), U2.2 (INOKB)
LX: C3.2, L1.2, U2.20 (LX), U2.21 (LX)
unnamed: C3.1, U2.1 (BST)
unnamed: C5.1, U2.17 (PVL)
unnamed: C9.1, R6.2, SW1.2
unnamed: C11.1, U2.10 (VDD)
unnamed: C12.1, C13.1, U2.22 (BYP)
unnamed: C21.2, L2.2, U4.3 (VDD3P3), U4.4 (VDD3P3)
unnamed: C25.2, L3.1, TP6.1
unnamed: D1.3 (RK), R3.1
unnamed: D1.4 (GK), R2.1
unnamed: F1.1, J1.A4 (VBUS), J1.A9 (VBUS), J1.B4 (VBUS), J1.B9 (VBUS)
unnamed: JP1.2 (C), U5.1 (~CS)
unnamed: Q1.2 (G), R4.2, R11.1, SW1.1
unnamed: Q1.4 (G), Q1.7 (D), Q1.8 (D), R1.2, R6.1
unnamed: Q2.1 (D), R15.2
unnamed: Q2.3 (G), R17.2, R19.2
unnamed: R7.1, U2.6 (DP)
unnamed: R8.1, U2.7 (DN)
unnamed: R9.2, U2.11 (ITOPOFF)
unnamed: R10.1, U2.12 (IFAST)
unnamed: R15.1, TFT1.11 (LEDK)
unnamed: RN1.1 (R1.1), U4.40 (SPIIO7,GPIO36,__FSPICLK)
unnamed: RN1.2 (R2.1), U4.39 (SPIIO6,GPIO35,__FSPID)
unnamed: RN1.3 (R3.1), U4.38 (SPIIO5,GPIO34,__FSPICS0)
unnamed: RN1.4 (R4.1), U4.37 (SPIIO4,GPIO33,__FSPIHD)
unnamed: RN2.1 (R1.1), U4.9 (RTC_GPIO4,___GPIO4,___TOUCH4,___ADC1_CH3)
unnamed: RN2.2 (R2.1), U4.8 (RTC_GPIO3,___GPIO3,___TOUCH3,___ADC1_CH2)
unnamed: RN2.3 (R3.1), U4.7 (RTC_GPIO2,___GPIO2,___TOUCH2,___ADC1_CH1)
unnamed: RN2.4 (R4.1), U4.6 (RTC_GPIO1,___GPIO1,___TOUCH1,___ADC1_CH0)
unnamed: RN3.1 (R1.1), U4.44 (MTDO,GPIO40,__CLK_OUT2)
unnamed: RN3.2 (R2.1), U4.43 (MTCK,GPIO39,__CLK_OUT3)
unnamed: RN3.3 (R3.1), U4.42 (GPIO38,__FSPIWP)
unnamed: RN3.4 (R4.1), U4.41 (SPIDQS,GPIO37,__FSPIQ)
unnamed: RN4.1 (R1.1), U4.13 (RTC_GPIO8,___GPIO8,___TOUCH8,___ADC1_CH7)
unnamed: RN4.2 (R2.1), U4.12 (RTC_GPIO7,___GPIO7,___TOUCH7,___ADC1_CH6)
unnamed: RN4.3 (R3.1), U4.11 (RTC_GPIO6,___GPIO6,___TOUCH6,___ADC1_CH5)
unnamed: RN4.4 (R4.1), U4.10 (RTC_GPIO5,___GPIO5,___TOUCH5,___ADC1_CH4)
PWRMAIN_SW: R11.2, RN1.8 (R1.2)
RX: J2.3, U4.48 (U0TXD,GPIO43,__CLK_OUT1)
SCL: RN6.2 (R2.1), U4.23 (TC_GPIO17,__GPIO17,__U1TXD,ADC2_CH6,__D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), U6.13 (SCL)
SDA: RN6.1 (R1.1), U4.24 (RTC_GPIO18,__GPIO18,__U1RXD,ADC2_CH7,__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), U6.14 (SDA)
SPICLK: U4.34 (SPICLK,GPIO30), U5.6 (SCK)
SPICS0: JP1.3 (B), U4.33 (SPICS0,GPIO29)
SPICS1: JP1.1 (A), U4.29 (SPICS1,GPIO26)
SPID: U4.36 (SPID,GPIO32), U5.5 (MOSI)
SPIHD: U4.31 (SPIHD,GPIO27), U5.7 (~HOLD)
SPIQ: U4.35 (SPIQ,GPIO31), U5.2 (MISO)
SPIWP: U4.32 (SPIWP,GPIO28), U5.3 (~WP)
STAT: R3.2, RN1.6 (R3.2), U2.3 (STAT)
SYS: C6.2, C7.2, D1.1 (A), L1.1, Q1.3 (1), R1.1, U2.15 (SYS), U2.16 (SYS)
SYSOUT: C4.2, H1.1, H6.1, Q1.5 (D), Q1.6 (D), R4.1, R5.1, U1.3 (EN), U1.4 (IN)
TX: J2.2, U4.49 (U0RXD,GPIO44,__CLK_OUT2)
U_N: R12.2, U4.25 (RTC_GPIO19,__GPIO19,__U1RTS,ADC2_CH8,__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)
U_P: R13.2, U4.26 (RTC_GPIO20,__GPIO20,__U1CTS,ADC2_CH9,__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)
VBUS: F1.2, U2.23 (VBUS), U2.24 (VBUS), U3.5 (VBUS)
VDD_SPI: C26.2, C27.2, U4.30 (VDD_SPI), U5.8 (VCC)
XTAL_N: C20.2, U4.52 (XTAL_N), Y1.1
XTAL_P: C14.1, U4.53 (XTAL_P), Y1.3
radio: C24.2, L3.2, U4.2 (LNA_IN)
